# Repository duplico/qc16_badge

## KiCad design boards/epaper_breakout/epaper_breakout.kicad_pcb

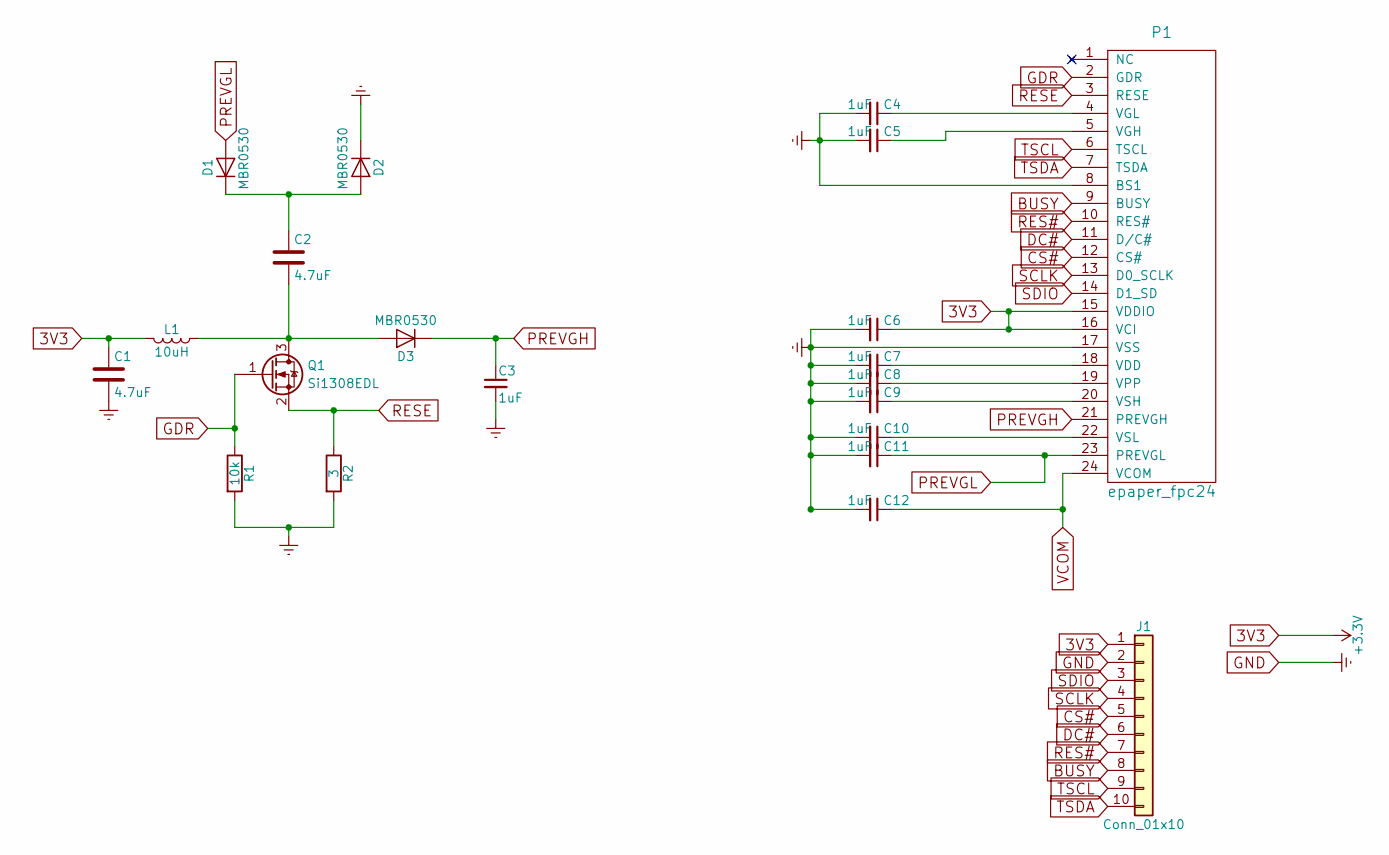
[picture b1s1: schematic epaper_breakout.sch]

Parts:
C1, C2: 4.7uF; C_0805_HandSoldering
C3, C4, C5, C6, C7, C8, C9, C10, C11, C12: 1uF; C_0805_HandSoldering
D1, D2, D3: MBR0530; D_SOD-123
J1: Conn_01x10; Socket_Strip_Straight_1x10_Pitch2.54mm
L1: 10uH; L_1210_HandSoldering
P1: epaper_fpc24; fpc24
Q1: Si1308EDL; SC-70-8_Handsoldering
R1: 10k; R_0805_HandSoldering
R2: 3; R_0805_HandSoldering

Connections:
3V3: C1.1, C6.1, J1.1, L1.2, P1.15 (VDDIO), P1.16 (VCI)
BUSY: J1.8, P1.9 (BUSY)
CS#: J1.5, P1.12 (CS#)
DC#: J1.6, P1.11 (D/C#)
GDR: P1.2 (GDR), Q1.1 (G), R1.1
GND: C1.2, C3.2, C4.2, C5.2, C6.2, C7.2, C8.2, C9.2, C10.2, C11.2, C12.2, D2.1 (K), J1.2, P1.8 (BS1), P1.17 (VSS), R1.2, R2.2
unnamed: C2.1, D1.1 (K), D2.2 (A)
unnamed: C2.2, D3.2 (A), L1.1, Q1.3 (D)
unnamed: C4.1, P1.4 (VGL)
unnamed: C5.1, P1.5 (VGH)
unnamed: C7.1, P1.18 (VDD)
unnamed: C8.1, P1.19 (VPP)
unnamed: C9.1, P1.20 (VSH)
unnamed: C10.1, P1.22 (VSL)
PREVGH: C3.1, D3.1 (K), P1.21 (PREVGH)
PREVGL: C11.1, D1.2 (A), P1.23 (PREVGL)
RES#: J1.7, P1.10 (RES#)
RESE: P1.3 (RESE), Q1.2 (S), R2.1
SCLK: J1.4, P1.13 (D0_SCLK)
SDIO: J1.3, P1.14 (D1_SD)
TSCL: J1.9, P1.6 (TSCL)
TSDA: J1.10, P1.7 (TSDA)
VCOM: C12.1, P1.24 (VCOM)

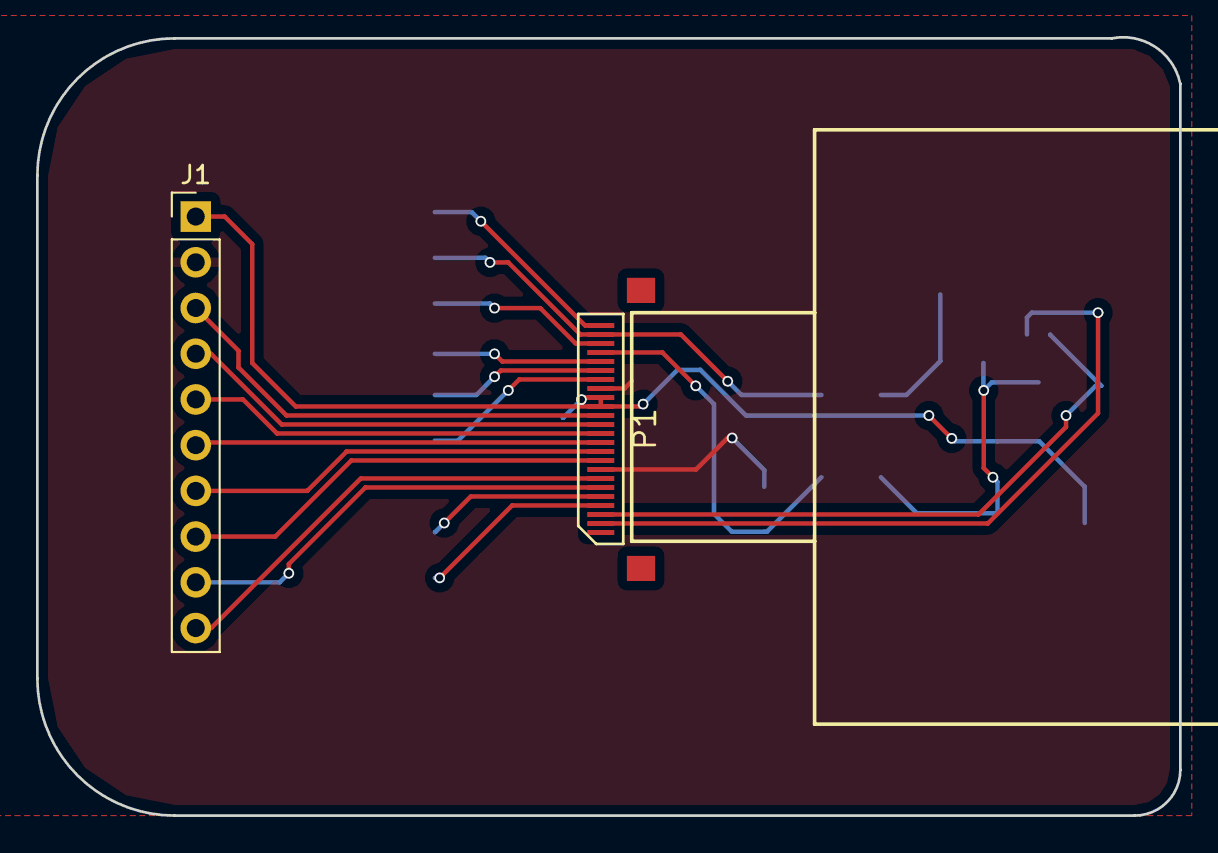
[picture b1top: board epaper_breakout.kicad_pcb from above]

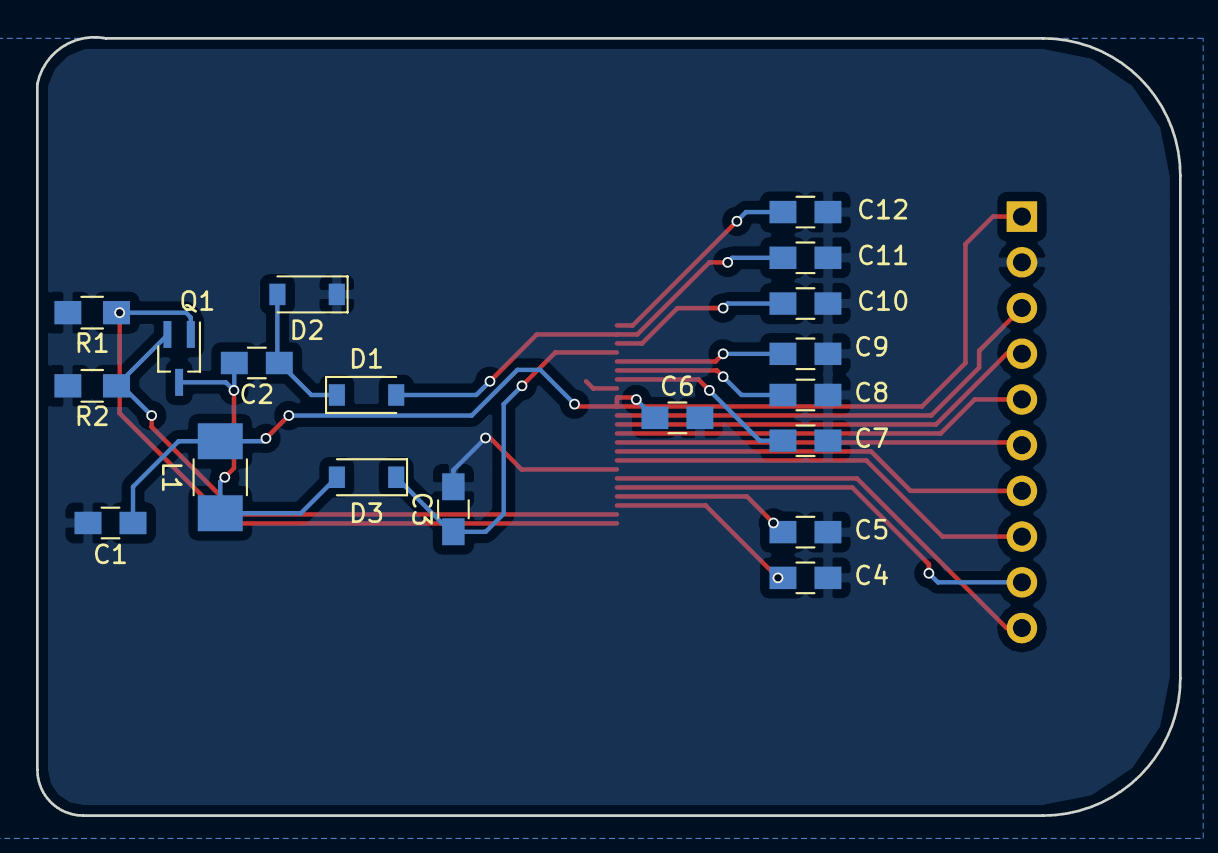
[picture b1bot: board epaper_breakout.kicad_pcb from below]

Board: 2 copper layers, 63.5 x 43.2 mm, 21 parts (19 on the bottom side), 23 nets.

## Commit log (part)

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2019-07-24 Improve serial validation.
2019-07-24 Controller improvements.
2019-07-24 Further serial validation.
2019-07-24 Correct length validation errors, per #282.
2019-07-24 Badge stats pulling from controller looks good.
2019-07-24 Promote/demote in controller seems working on cbadges.
2019-07-24 I think all that's left on the cbadges is to do the animations/LED work?
    I mean, plus all the bugs that are probably there.
2019-07-24 Adjust indexes, fixing an overrun issue.
2019-07-24 Save after doing a mission.
2019-07-24 Add and test handle-setting in the controller.
2019-07-24 Space optimizations.
2019-07-25 Add a lot of cbadge animations, plus some size optimizations.
2019-07-25 Turn off the LEDs once we have an initial ID.
2019-07-25 Animation declaration.
2019-07-25 Connection idle animation fix.
2019-07-25 Fix location of animation ending code.
2019-07-25 Fix button release.
2019-07-25 Make an animation if we power-up.
2019-07-25 Increase precision of LED brightness.
2019-07-25 First draft queercon nameplate.
2019-07-25 Revert PWM resolution.
2019-07-25 Animation and other fixes, but file is slightly too big.
2019-07-25 Shrink code size.
2019-07-25 Add a disconnect flag to the main loop.
2019-07-25 Clean up dead/useless code.
2019-07-25 Consume the disconnect flag.
2019-07-25 Make a badge temporarily active when plugged into a powered cbadge.
2019-07-25 Active badge animation cleanup
2019-07-25 Increase and fix PHY timeout on TX (in PTX).
2019-07-25 Fix the not-in-service lighting setup.
2019-07-25 Clear the disconnect signal at the end of its block, per our convention.
2019-07-25 Clear our selected icon when pairing with a qbadge.
2019-07-25 Add a caveat about the way the cbadge serial RX works.
2019-07-25 Display the mission-going blink, and clear my icon (except when leveling up).
2019-07-25 Handle starts out blank.
2019-07-25 Process TODOs.
2019-07-25 Rearrange where element-selected clearing happens.
2019-07-25 Remove dead code, reduce image size.
2019-07-26 Correct minor mission-level checking bug.
2019-07-26 Keep config.
2019-07-26 Fix a buffer alignment in checking mission levels.
2019-07-26 Remove spurious comment.
2019-07-26 Combine some animations and writes to save a bit of flash.
2019-07-26 Fix a pointer error, and correctly share our stats (oops!)
2019-07-26 Don't always turn off animations on disconnection.
2019-07-26 Added tag cbadge-rc1 for changeset 88c9b47ca1cc
2019-07-26 Fix BLE frame size/indices
2019-07-26 Add a new_connection flag to signal cbadges that they've met someone new.
2019-07-26 Added tag cbadge-rc2 for changeset 6846b678e5df
2019-07-26 Update build guide.
2019-07-27 Move the initialization of events and EPD to precede the threads.
2019-07-27 Re-arrange everything so the UI task bootstraps the launch of the program.
2019-07-27 Complete POST routine.
2019-07-27 Move LED init before POST display, so that we can actually see errors.
2019-07-27 Implement verification routine.
2019-07-28 Add verification outputs.
2019-07-28 Add a test nameplate.
2019-07-28 Fix a wrong length in the advertisement data.
2019-07-29 Correct an index in the BLE advertisement, resolving #293.
2019-07-29 Bring in the production nameplates.
2019-07-29 Only update battery display in HUD if it's a huge change, resolving #283.
2019-07-29 Various pairing/serial fixes, resolving #279.
2019-07-29 Add a battery low event, and configure for the LF RCOSC.
2019-07-29 All colors are now 8-bit (6-bit) with a max value of 63, resolving #56.
2019-07-29 Dramatically improve the performance of the light sensor and sidelights.
2019-07-29 I like this approach to brightness adjustment *dramatically better*.
2019-07-29 Light adjustment improvements.
2019-07-30 Try to detect a super full flash chip.
2019-07-30 New approach to tracking badges seen. BLE seems to have stopped listening...
2019-07-30 Toward production icons.
2019-07-30 Update to latest SDK.
2019-07-30 Connection tracking seems working.
2019-07-30 Mark badges seen if they're connected.
2019-07-30 Improve the POST display.
2019-07-30 Full refresh on textbox unload, resolving #295.
2019-07-30 Adjust fixed text size, resolving #288.
2019-07-30 Track nearest handler.
2019-07-30 Report nearest handler.
2019-07-30 Use the nearby handler's name in the hud.
2019-07-30 Forbid renaming protected or superprotected files.
2019-07-30 Allow handle changing from file menu, resolving #176.
2019-07-30 First draft, keypad application jig.
2019-07-30 Attempt to do some typematic stuff.
2019-07-30 Shorten broadcast data; apparently it doesn't like 31-bytes.
2019-07-30 Fix character order.
2019-07-30 Keep the typematic, but adjust interval for better performance.
2019-07-30 Remove dead code.
2019-07-30 Remove dead comment.
2019-07-30 Process and clear TODOs.
2019-07-30 Get both rewards (but not progress) for double-Q missions, resolving #242.
2019-07-30 Add a 1-min cooldown to getting missions from a human handler, resolving #179.
2019-07-30 Implement cbadge level capacity boost, resolving #115.
2019-07-30 Update badgelife appearance, resolving #206.
2019-07-30 Correct Endian-ness of badgelife header.
2019-07-30 Human handler missions.
2019-07-30 Fix a config regeneration.
2019-07-30 Fix BLE parameter.
2019-07-30 Bias handler missions' second elements towards cbadge complement.
2019-07-30 Remove NO_ROM, resolving #11.
2019-07-30 Idle timeout of sidelights, resolving #298.
2019-07-30 Substantially dim the element LEDs, resolving #287.
2019-07-30 Guarantee (inject) a null term to the BLE name, resolving #207.
2019-07-30 Assert that the badge name is the correct length in a BLE advertisement.
2019-07-30 Test null terms in a BLE name, and it seems ok.
2019-07-31 Fix handle setting to BLE.
2019-07-31 Detect DCFurs.
2019-07-31 Add note about an LED error condition.
2019-07-31 Add stubs for the pair file and cbadge info menus.
2019-07-31 Reorganize cbadge pair menu item into just a handle-setter.
2019-07-31 Add signaling between UI and serial for new actions.
2019-07-31 Implement cbadge handle-setting.
2019-07-31 File reading from badge seems working.
2019-07-31 Fix handler appearance.
2019-07-31 Implement outstanding controller items, resolving #305
2019-07-31 Guard against a CRC error that will probably never happen.
2019-07-31 Badge to badge file transfer is working.
2019-07-31 Protected files, resolving #224.
2019-07-31 File transfers protected and working reasonably well.
2019-07-31 Prevent an 8-bit integer overflow. Damn!!!
2019-07-31 Accept a promotion message.
2019-07-31 Change our small fixed font.
2019-07-31 Actually honor the handler cooldown.
2019-07-31 Modifier and type logic working correctly in colorpicker.
2019-07-31 Next keypad jig iteration.
2019-07-31 Implement sixon, scroll, and bubble.
2019-07-31 Fast and slow modifiers, and panes.
2019-07-31 All animation types done.
2019-07-31 Animating flag modifier working.
2019-07-31 New keyboard jig draft.
2019-07-31 Correct on-screen flag display of non-animating colors.
2019-07-31 Tighten PCB tolerances.
2019-08-01 Dim the colorpicking lights, resolving #57.
2019-08-01 Improve the color sequence, resolving #229 and #312.
2019-08-01 Bring in a nearly final draft of art.
2019-08-01 Update spreadsheet.
2019-08-01 Add arrows to the colorpicker selectors.
2019-08-01 Set production uber/handler counts.
2019-08-01 Fix uber plate.
2019-08-01 Fix cooldown.
2019-08-01 Cleanup art.
2019-08-01 Fix an SWI race condition.
2019-08-01 Increase minimum brightness, resolving #328.
2019-08-01 Brighter yet.
2019-08-01 Switch sidelights off when needed, resolving #329.
2019-08-01 Be more eager to disable the sidelights if the dustbuster is off.
2019-08-01 Perform some very very basic conf validation in load_conf.
2019-08-01 Improve HUD appearance.
2019-08-01 Additional battery cutoff protection.
2019-08-01 Adjust centering for radar counter.
2019-08-01 Create starting animation.
2019-08-01 FINE, I'll add a time virus.
2019-08-01 Fix a warning.
2019-08-01 Unlock the flag wave animation at Thursday's party.
2019-08-01 I think this is the keypad jig.
2019-08-01 Fix a handler cooldown bug.
2019-08-01 Actually listen for more handlers after the first 45 seconds or whatever.
2019-08-01 Fix brightness.
2019-08-01 Add placeholder for the startup sequence.
2019-08-01 Tune and fix mission values.
2019-08-01 Send an update message if the handler returns to our badge during pairing.
2019-08-01 Bounds and frame size checking.
2019-08-01 Call the cold and hot stubs.
2019-08-01 Adjust brightness.
2019-08-01 Protect all calls to malloc and free from Hwi clobbers.
2019-08-01 Just change some comments.
2019-08-01 Switch abort function (at least for now)
2019-08-01 Fix validation.
2019-08-01 Add some extra basic validation to the BLE.
2019-08-01 Add some more checks to our radar buffers.
2019-08-01 Fix a stack overrun.
2019-08-02 Add badge-element-nearby tracking and implement the scan menu.
2019-08-02 Set levels in BLE beacon, resolving #337.
2019-08-02 detect boop badges, resolving #208
2019-08-02 Toward a proper startup/flashing experience.
2019-08-02 Fix reformer order for landscape.
2019-08-02 Do the initial setup process. Not my finest work, but... oh well.
2019-08-02 Record total elements and missions run stats.
2019-08-02 Set up twinkly modifiers.
2019-08-02 Pulse lights during a mission.
2019-08-02 Add a bunch of notification animations.
2019-08-02 0 is a valid SPIFFS file descriptor.
2019-08-02 Fix file name disambiguation.
2019-08-02 Dead code.
2019-08-02 Correct an unlock.
2019-08-02 Correct the rainbow animation unlock.
2019-08-02 Make level 0 cbadge missions more common.
2019-08-02 Fix file ordering/rendering bug.
2019-08-02 Add the code.
2019-08-02 Cleanup to prep for shipping.
2019-08-02 Make twinkle mods work on the static color types.
2019-08-02 Stats
2019-08-02 Stats display and scan improvement.
2019-08-02 Improve scan appearance.
2019-08-02 Fix bug in the chip code.
2019-08-03 Add production materials and qautoid to controller.
2019-08-06 Fix a bug that we shipped with.
2019-08-06 Update documentation.
2019-08-07 Art and docs.
